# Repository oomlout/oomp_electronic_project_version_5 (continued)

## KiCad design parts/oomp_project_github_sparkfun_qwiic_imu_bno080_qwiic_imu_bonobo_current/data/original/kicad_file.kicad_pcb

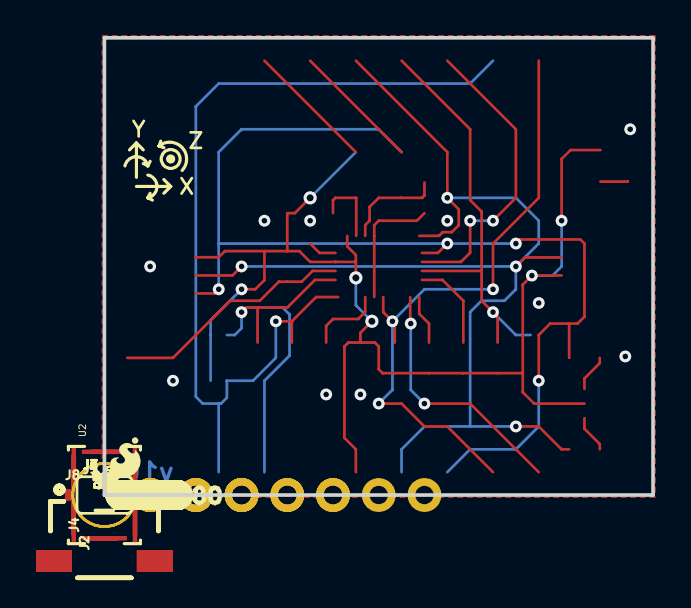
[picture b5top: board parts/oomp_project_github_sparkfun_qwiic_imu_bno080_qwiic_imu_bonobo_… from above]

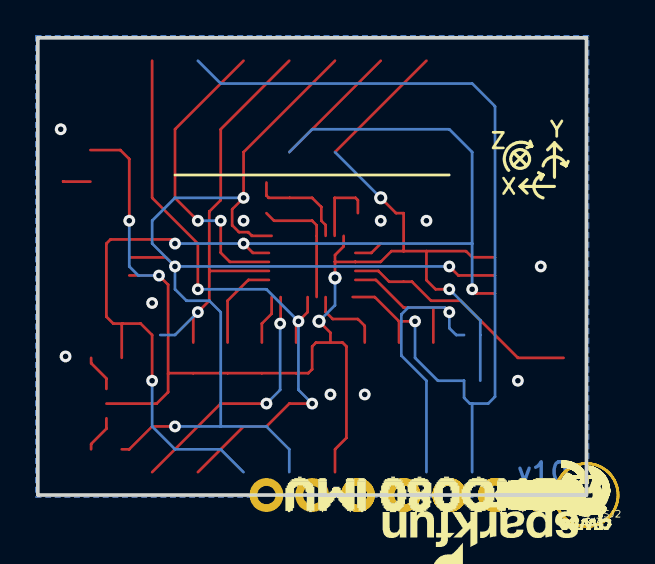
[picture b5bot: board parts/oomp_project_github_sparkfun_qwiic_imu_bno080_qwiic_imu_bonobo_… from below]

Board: 2 copper layers, 30.5 x 25.4 mm, 89 parts (35 on the bottom side), 19 nets.

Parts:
C1, C2, C4: 0.1uF; 0603
C3, C5: 22pF; 0603
D1: RED; LED-0603
FRAME1: FRAME-LETTER; CREATIVE_COMMONS
J1: 1X06_NO_SILK
J2, J4: SMD; 1X04_1MM_RA
J3: PTH; 1X04_NO_SILK
J5: 1X01_NO_SILK
J6: SPI; 1X08_NO_SILK
J7, J8: 1X02_NO_SILK
JP1, JP2, JP5, JP6: FIDUCIALUFIDUCIAL; MICRO-FIDUCIAL
JP3, JP4: STAND-OFF
LOGO1: OSHW-LOGOMINI; OSHW-LOGO-MINI
LOGO2: REVISION
LOGO4: SFE_LOGO_FLAME.1_INCH; SFE_LOGO_FLAME_.1
LOGO5: SFE_LOGO_NAME_FLAME.1_INCH; SFE_LOGO_NAME_FLAME_.1
R1, R3, R6, R7, R8: 10k; 0603
R2: 1k; 0603
R9, R10: 4.7k; 0603
R12, R13: 2.2k; 0603
SJ1: SMT-JUMPER_3_2-NC_PASTE_SILK
SJ2, SJ3, SJ4: SJ_2S-NO
U2: BNO080; LGA-28
U$1: (PWR)
U$2: BOOT2
U$3, U$4: #RST_
U$5, U$6: SCL
U$7, U$8: SDA
U$9, U$10: 3V3
U$11, U$50: 3V30
U$12, U$13: SCK0
U$14: PS03
U$15, U$16: GND
U$17, U$18: SI1
U$19, U$20: #WAK6
U$21: 3V32
U$22: RXI1
U$23: (I_SUPER2_C)
U$25, U$26: #INT0
U$27, U$28: PS14
U$29: PS05
U$30: ADR0
U$33: PS114
U$34: PS015
U$35: TXO0
U$39: UART8
U$40: GRN10
U$41: BLK9
U$42, U$43: GND1
U$44: BNO080_IMU11
U$46: BNO08012
U$47: IMU13
U$49, U$51: #RST7
U$52, U$53: #CS3
U$54, U$55: SO0
U$59: QWIIC#LABEL#FULL#M#PNG
Y1: 32.768kHz; CRYSTAL-SMD-3.2X1.5MM

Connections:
3.3V: C2.1, C4.1, D1.A, J1.3, J2.2, J3.2, J4.2, J6.2, R1.2, R3.2, R6.2, R9.2, R10.2, SJ1.2, SJ3.1, SJ4.1, U2.3, U2.28
ADDR/MOSI: J6.5, R3.1, SJ2.2, U2.17
CAP: C1.1, U2.9
GND: C1.2, C2.2, C3.2, C4.2, C5.2, J1.1, J2.1, J3.1, J4.1, J6.1, R2.1, R7.1, R8.1, SJ2.1, U2.2, U2.10, U2.25
unnamed: C5.1, U2.27, Y1.P$2
unnamed: C3.1, U2.26, Y1.P$1
unnamed: D1.C, R2.2
PS0/WAKE: J6.7, J8.2, R7.2, SJ3.2, U2.6
PS1: J8.1, R8.2, SJ4.2, U2.5
SCL/SCK/RX: J1.4, J2.4, J3.4, J4.4, J6.3, R12.1, U2.19
SCL_PU: R12.2, SJ1.1
SDA/MISO/TX: J1.5, J2.3, J3.3, J4.3, J6.4, R13.1, U2.20
SDA_PU: R13.2, SJ1.3
S_SCL: R10.1, U2.15
S_SDA: R9.1, U2.16
~BOOT: J5.1, R6.1, U2.4
~CS: J6.6, U2.18
~INT: J7.2, U2.14
~RST: J6.8, J7.1, R1.1, U2.11

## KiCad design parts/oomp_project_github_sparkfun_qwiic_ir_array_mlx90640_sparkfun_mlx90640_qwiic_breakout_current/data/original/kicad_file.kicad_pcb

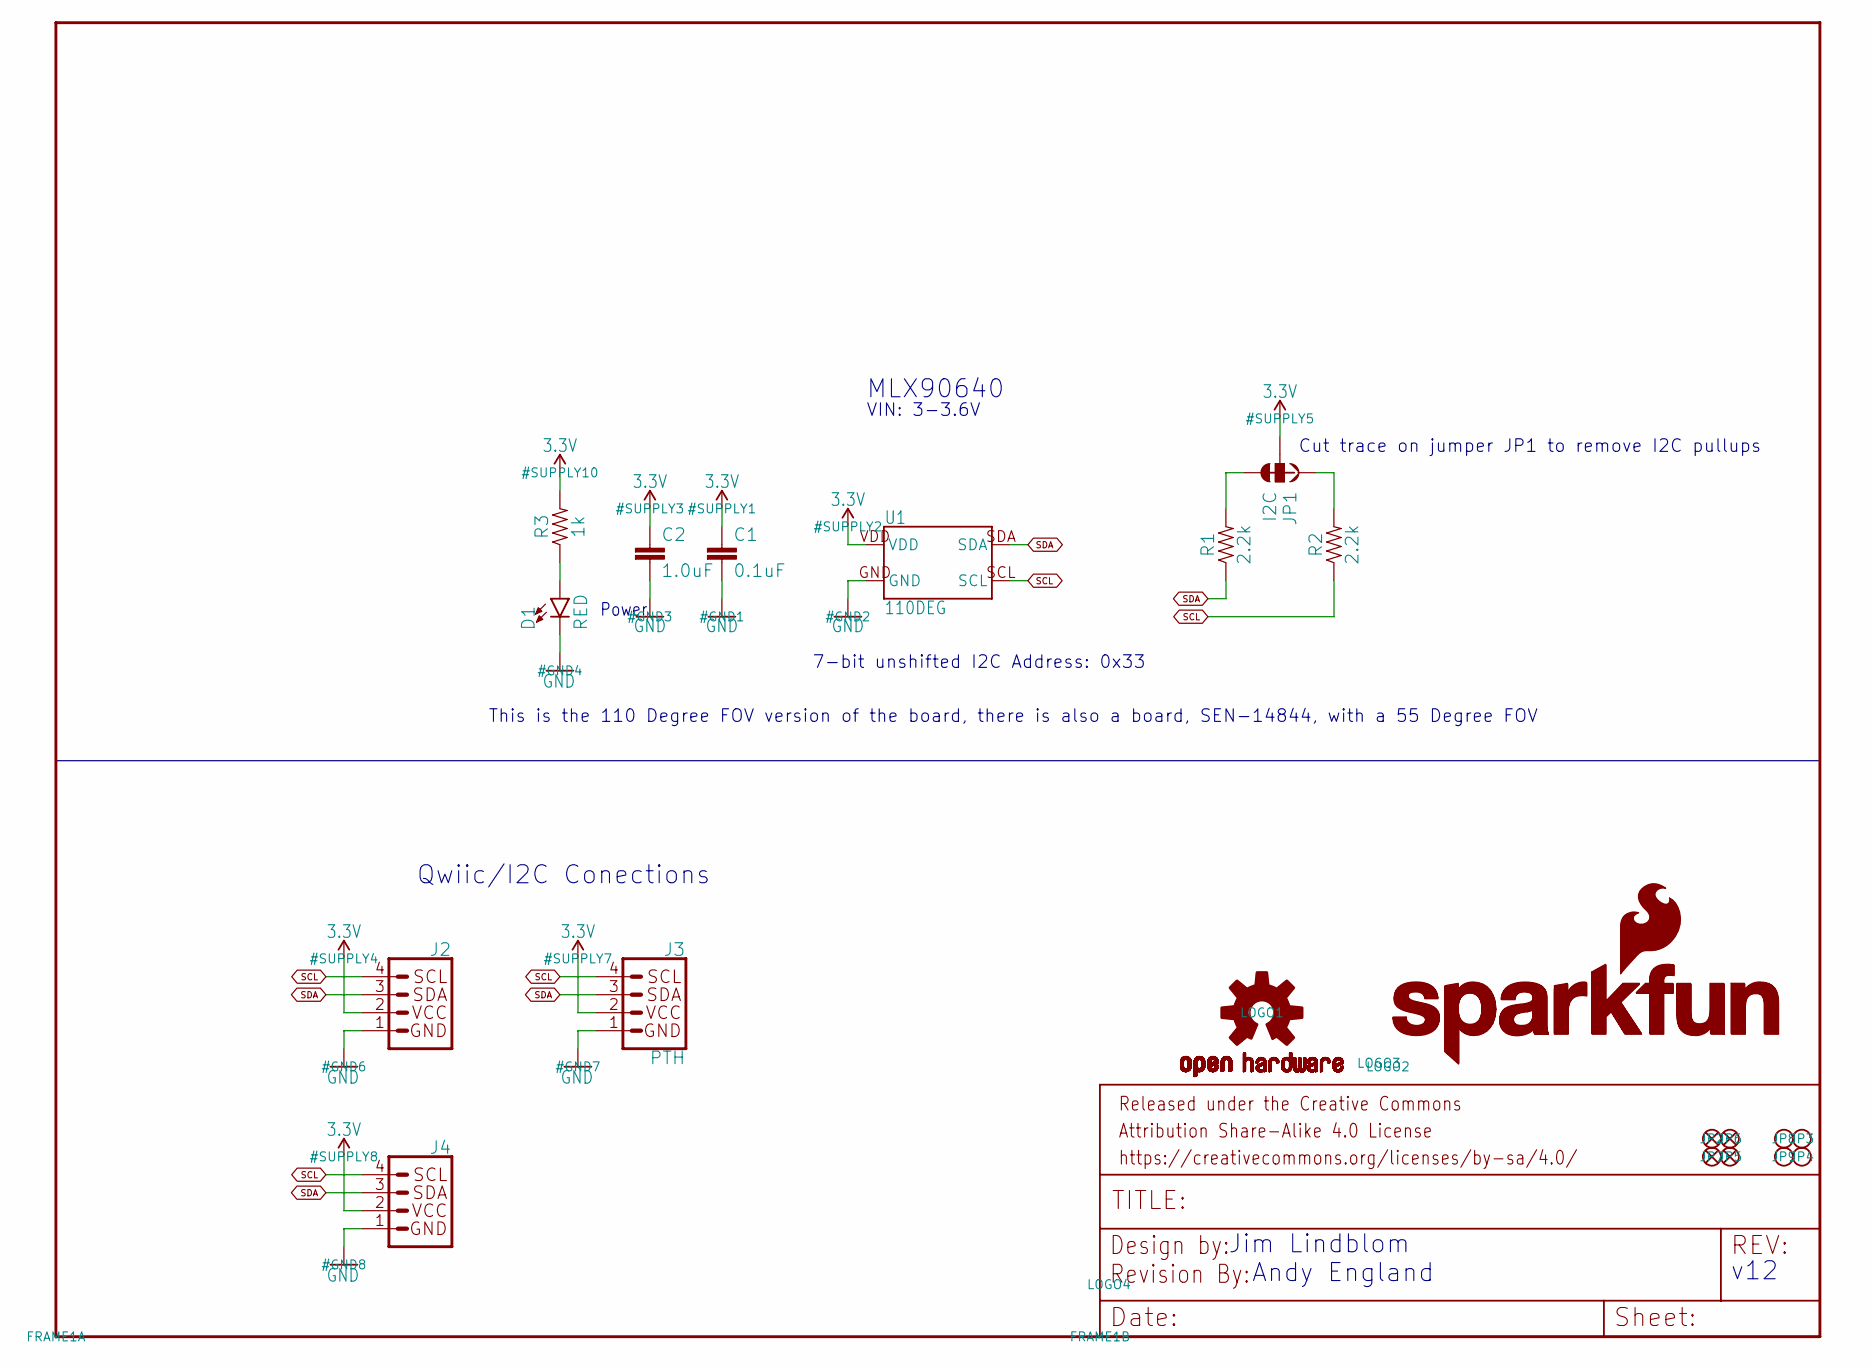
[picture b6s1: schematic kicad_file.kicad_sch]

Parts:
C1: 0.1uF; 0603
C2: 1.0uF; 0603
D1: RED; LED-0603
FRAME1: FRAME-LETTER; CREATIVE_COMMONS
J2, J4: QWIIC_CONNECTORJS-1MM; JST04_1MM_RA
J3: PTH; 1X04_NO_SILK
JP1: I2C; SMT-JUMPER_3_2-NC_TRACE_NO-SILK
JP2, JP5, JP6, JP7: FIDUCIALUFIDUCIAL; MICRO-FIDUCIAL
JP3, JP4, JP8, JP9: STAND-OFF
LOGO1: OSHW-LOGOMINI; OSHW-LOGO-MINI
LOGO2: SFE_LOGO_NAME_FLAME.1_INCH; SFE_LOGO_NAME_FLAME_.1
LOGO3: SFE_LOGO_NAME.1_INCH; SFE_LOGO_NAME_.1
LOGO4: REVISION
R1, R2: 2.2k; 0603
R3: 1k; 0603
U1: 110DEG; MLX90540_MLX90640

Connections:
3.3V: C1.1, C2.1, J2.2, J3.2 (VCC), J4.2, JP1.2, R3.2, U1.VDD
GND: C1.2, C2.2, D1.C, J2.1, J3.1 (GND), J4.1, U1.GND
unnamed: JP1.3, R1.2
unnamed: JP1.1, R2.2
unnamed: D1.A, R3.1
SCL: J2.4, J3.4 (SCL), J4.4, R2.1, U1.SCL
SDA: J2.3, J3.3 (SDA), J4.3, R1.1, U1.SDA

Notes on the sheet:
Cut trace on jumper JP1 to remove I2C pullups
7-bit unshifted I2C Address: 0x33
Jim Lindblom
VIN: 3-3.6V
MLX90640
Power
v12
This is the 110 Degree FOV version of the board, there is also a board, SEN-14844, with a 55 Degree FOV
Qwiic/I2C Conections
Andy England

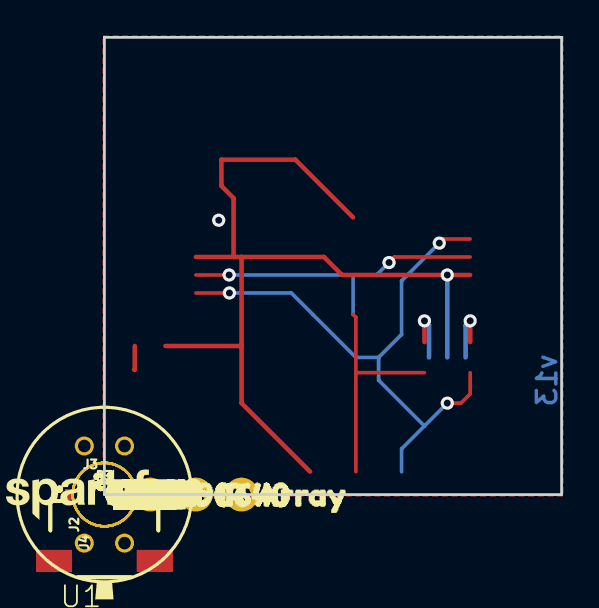
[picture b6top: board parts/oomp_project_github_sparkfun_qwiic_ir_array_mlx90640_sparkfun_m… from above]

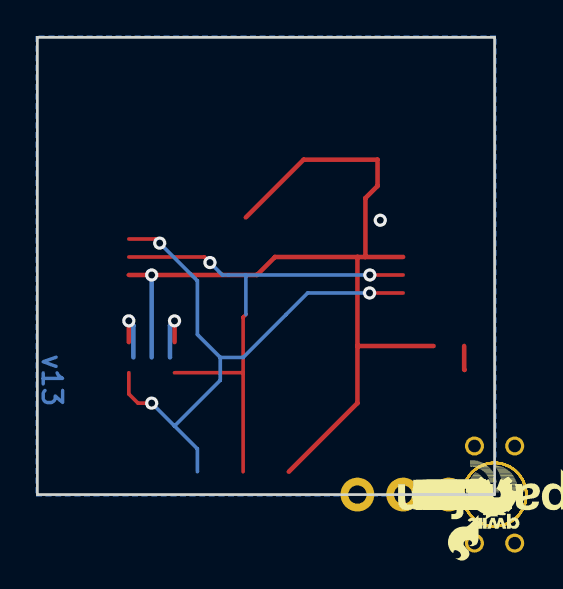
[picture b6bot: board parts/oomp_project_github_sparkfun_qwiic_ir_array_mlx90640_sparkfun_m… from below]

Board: 2 copper layers, 25.4 x 25.4 mm, 39 parts (11 on the bottom side), 7 nets.

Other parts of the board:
U$1, U$7: SDA-[)
U$3: 55X35#1
U$4, U$8: SCL-[)
U$5, U$9: 3.3V
U$6, U$10: GND-04
U$11: QWIIC-LOGO-SMALL
U$12: PWR-()-03
U$13: MLX906401
U$14: QWIIC_IR_ARRAY0
U$15: 110X75#0
U$16: I_SUPER2_C-()-03

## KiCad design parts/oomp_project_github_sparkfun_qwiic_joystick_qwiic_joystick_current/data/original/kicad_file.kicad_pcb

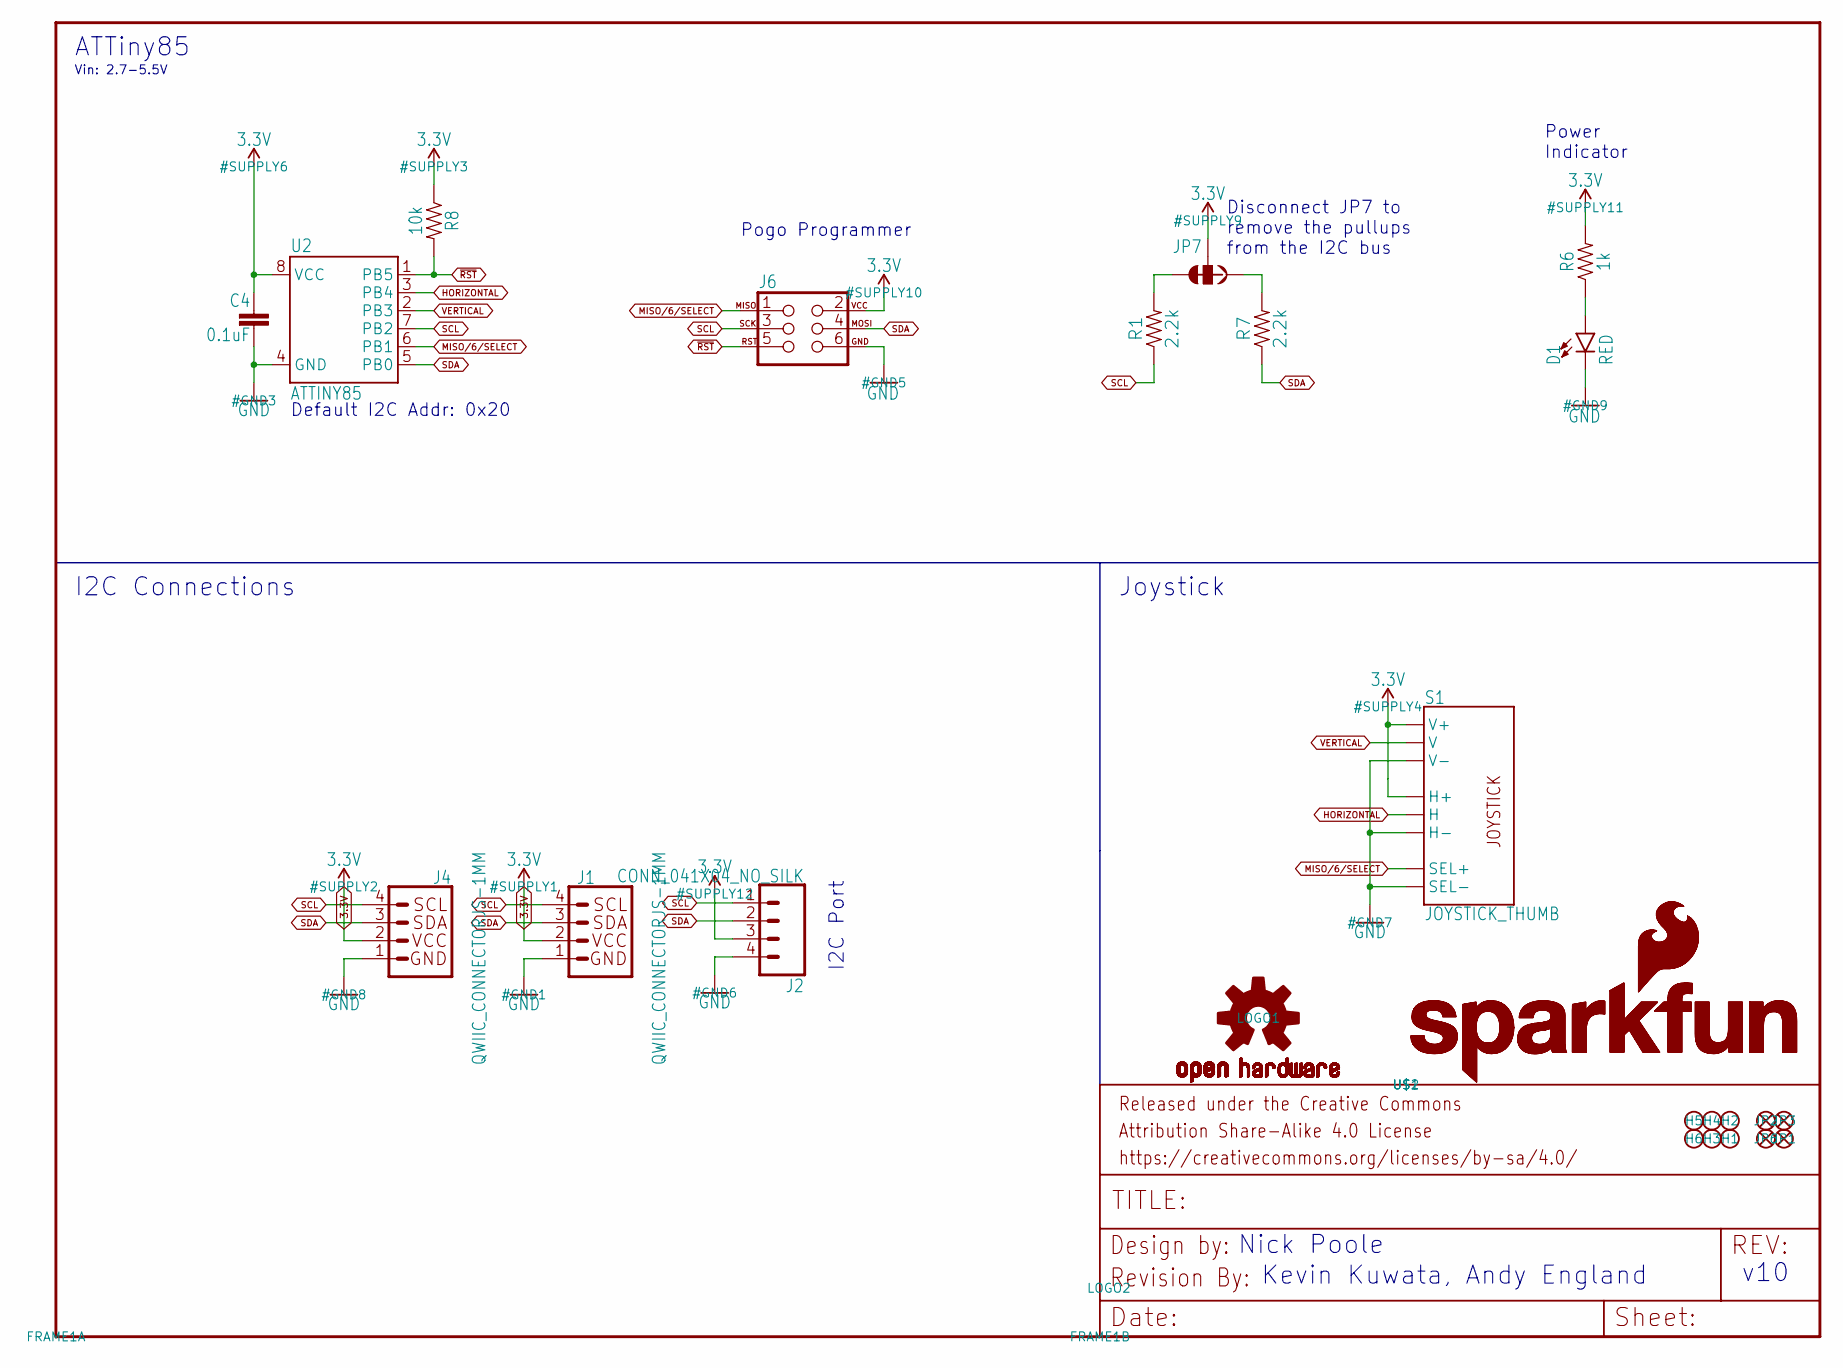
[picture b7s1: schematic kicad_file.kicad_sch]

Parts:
C4: 0.1uF; 0603
D1: RED; LED-0603
FRAME1: FRAME-LETTER; CREATIVE_COMMONS
H1, H2, H3, H4, H5, H6: STAND-OFF
J1, J4: QWIIC_CONNECTORJS-1MM; 1X04_1MM_RA
J2: CONN_041X04_NO_SILK; 1X04_NO_SILK
J6: AVR_SPI_PROG_3X2TESTPOINTS; 2X3_TEST_POINTS
JP1, JP2, JP3, JP6: FIDUCIALUFIDUCIAL; MICRO-FIDUCIAL
JP7: JUMPER-SMT_3_2-NC_TRACE_NO-SILK; SMT-JUMPER_3_2-NC_TRACE_NO-SILK
LOGO1: OSHW-LOGOMINI; OSHW-LOGO-MINI
LOGO2: REVISION
R1, R7: 2.2k; 0603
R6: 1k; 0603
R8: 10k; 0603
S1: JOYSTICK_THUMB; JOYSTICK
U2: ATTINY85
U$1, U$2: SFE_LOGO_NAME_FLAME.1_INCH; SFE_LOGO_NAME_FLAME_.1

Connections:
3.3V: C4.1, J1.2, J2.3, J4.2, J6.2, JP7.2, R6.2, R8.1, S1.H1 (H+), S1.V1 (V+), U2.8 (VCC)
GND: C4.2, D1.C, J1.1, J2.4, J4.1, J6.6, S1.B2A (SEL-), S1.H3 (H-), S1.V3 (V-), U2.4 (GND)
HORIZONTAL: S1.H2 (H), U2.3 (PB4)
MISO/6/SELECT: J6.1, S1.B1A (SEL+), U2.6 (PB1)
unnamed: D1.A, R6.1
unnamed: JP7.1, R7.2
unnamed: JP7.3, R1.2
SCL: J1.4, J2.1, J4.4, J6.3, R1.1, U2.7 (PB2)
SDA: J1.3, J2.2, J4.3, J6.4, R7.1, U2.5 (PB0)
VERTICAL: S1.V2 (V), U2.2 (PB3)
~RST: J6.5, R8.2, U2.1 (PB5)

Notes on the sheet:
I2C Connections
ATTiny85
Vin: 2.7-5.5V
Default I2C Addr: 0x20
I2C Port
Power Indicator
Disconnect JP7 to remove the pullups from the I2C bus
v10
Joystick
Pogo Programmer
Kevin Kuwata, Andy England
Nick Poole

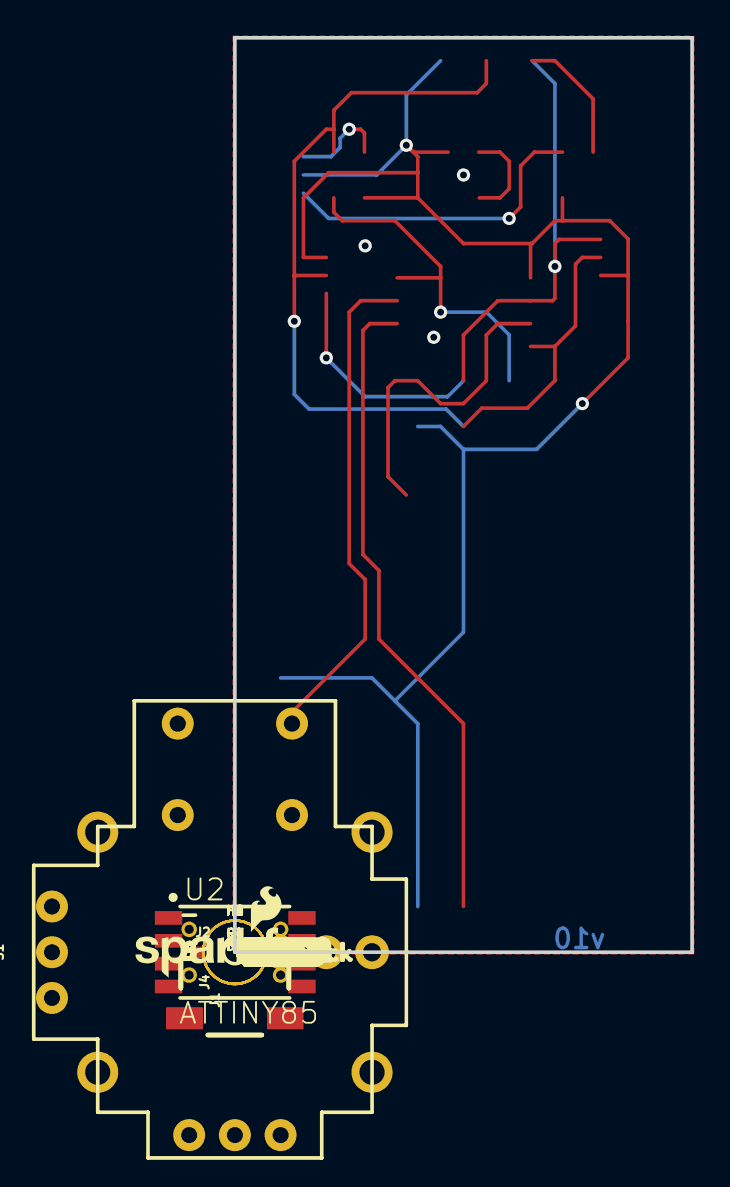
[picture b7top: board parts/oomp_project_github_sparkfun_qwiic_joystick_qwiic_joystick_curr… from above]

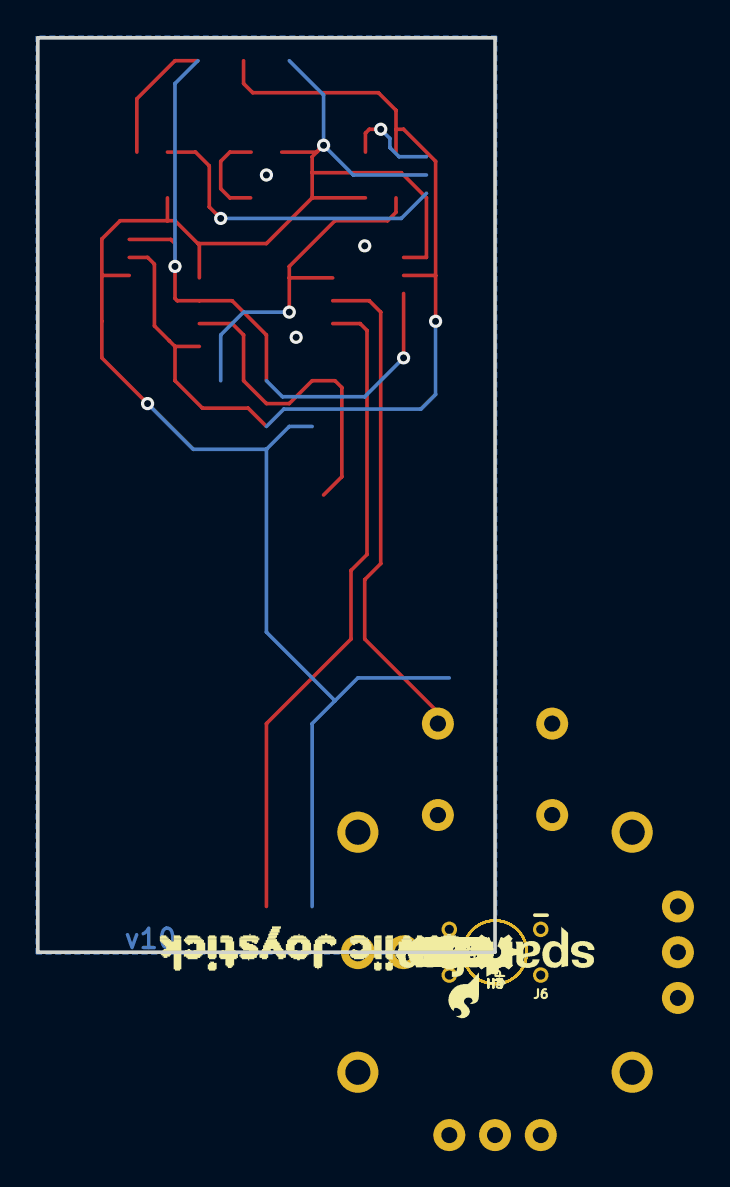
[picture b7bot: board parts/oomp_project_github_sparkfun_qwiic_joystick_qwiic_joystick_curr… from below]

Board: 2 copper layers, 25.4 x 50.8 mm, 43 parts (14 on the bottom side), 11 nets.

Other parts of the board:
U$3: QWIIC0
U$4: I2C_PU0
U$5: SDA0
U$6, U$8: GND4
U$7: ##V##1
U$9: SCL1
U$10: JOYSTICK0
U$11: SCL3
U$12: SDA2
U$13: QWIIC_JOYSTICK1
U$14: PWR-()-03
U$15: ##H##0
U$16, U$17: 3V35

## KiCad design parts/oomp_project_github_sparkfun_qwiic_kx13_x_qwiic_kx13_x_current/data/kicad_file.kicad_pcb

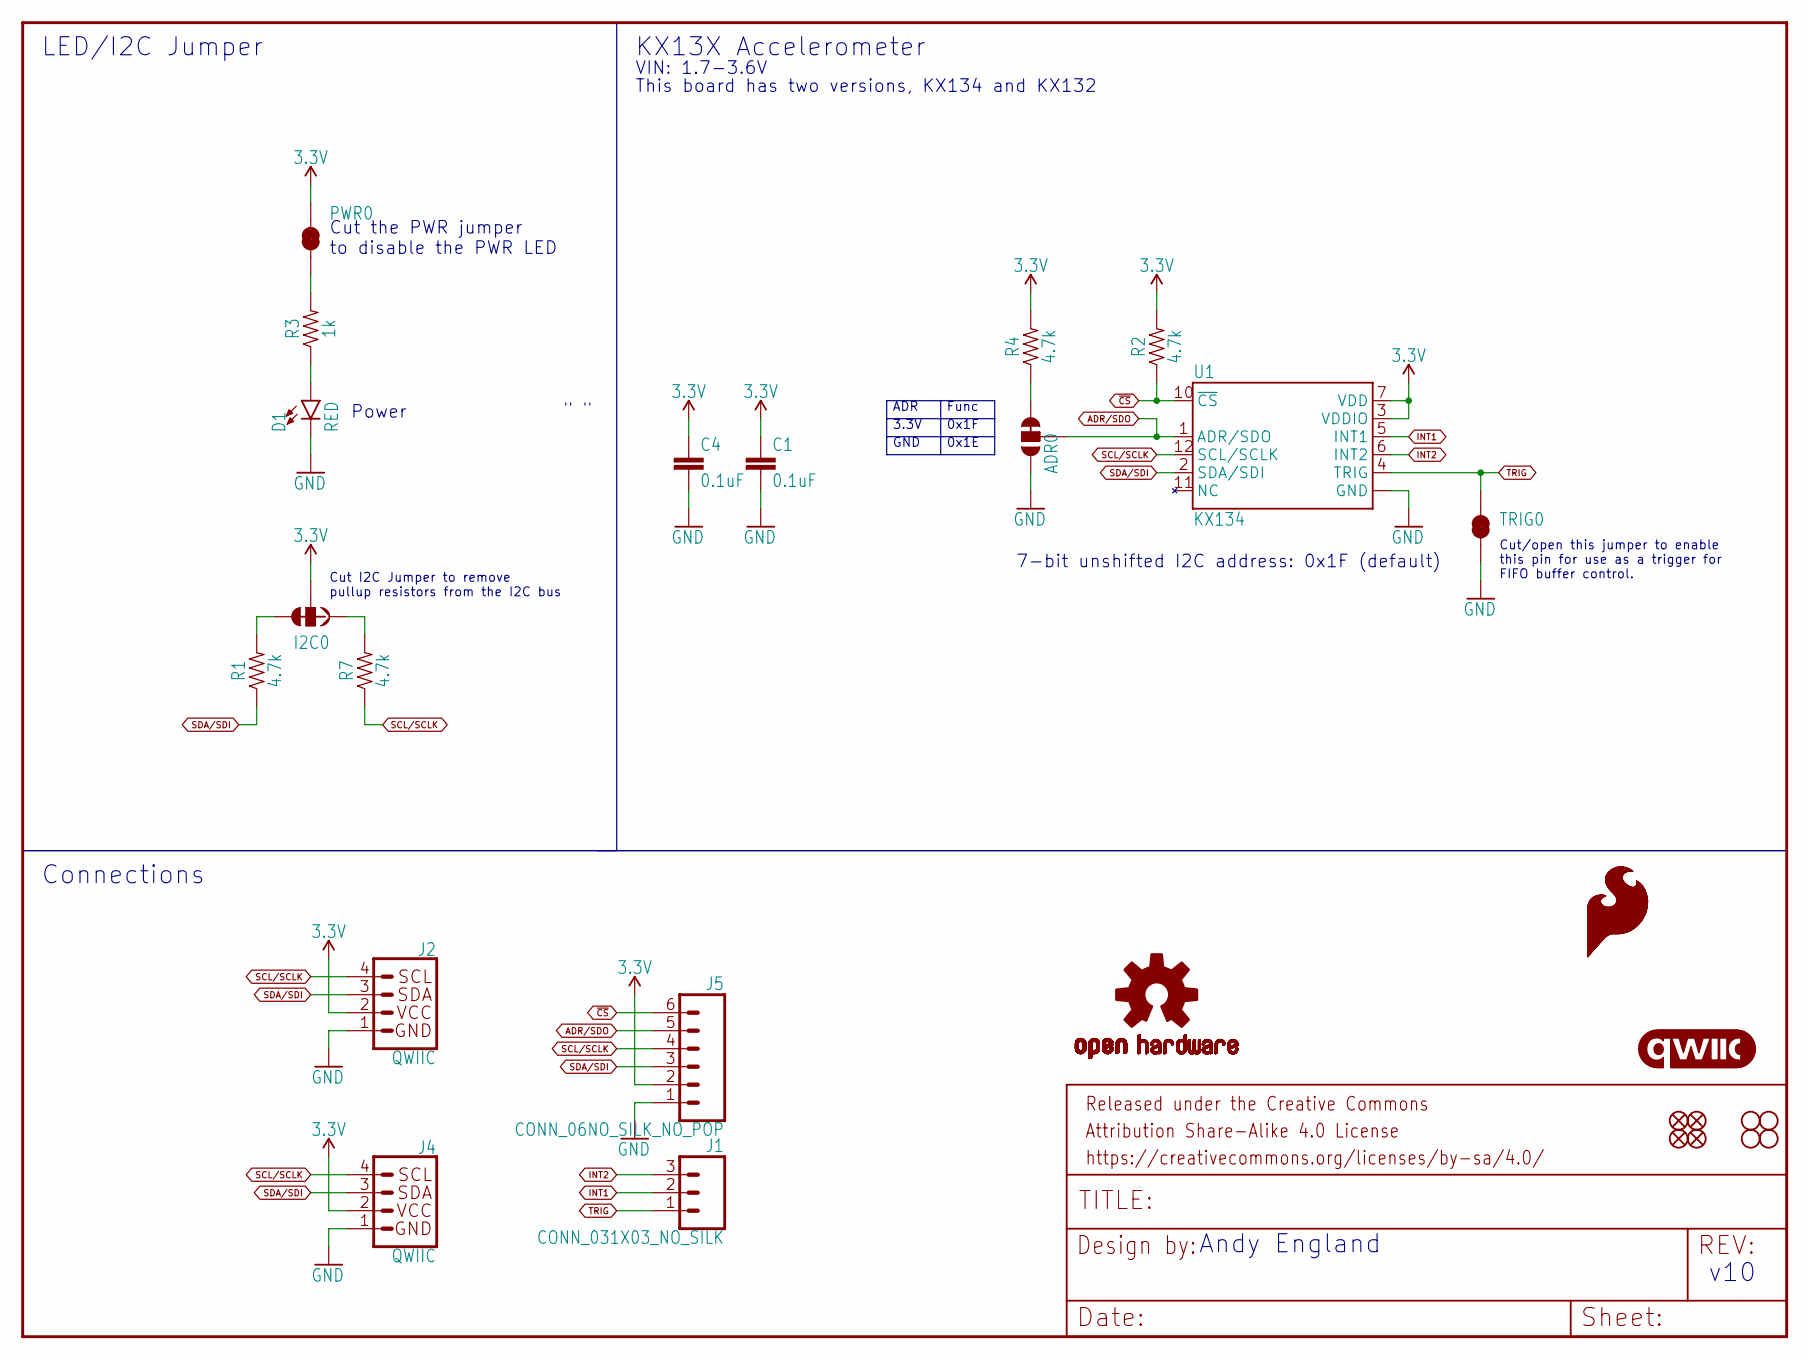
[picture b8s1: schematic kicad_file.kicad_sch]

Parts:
ADR0: JUMPER-SMT_3_1-NC_TRACE_SILK; SMT-JUMPER_3_1-NC_TRACE_SILK
C1, C4: 0.1uF; 0603
D1: RED; LED-0603
FRAME1: FRAME-LETTER; CREATIVE_COMMONS
I2C0: JUMPER-SMT_3_2-NC_TRACE_SILK; SMT-JUMPER_3_2-NC_TRACE_SILK
J1: CONN_031X03_NO_SILK; 1X03_NO_SILK
J2, J4: QWIIC; JST04_1MM_RA
J5: CONN_06NO_SILK_NO_POP; 1X06_NO_SILK
JP1, JP2, JP5, JP6: FIDUCIALUFIDUCIAL; MICRO-FIDUCIAL
JP3, JP4, JP7, JP8: STAND-OFF
LOGO1, LOGO2: SFE_LOGO_FLAME.1_INCH; SFE_LOGO_FLAME_.1
LOGO3: QWIIC_LOGO_4MM; QWIIC_4MM
LOGO5: OSHW-LOGOS; OSHW-LOGO-S
PWR0: JUMPER-SMT_2_NC_TRACE_SILK; SMT-JUMPER_2_NC_TRACE_SILK
R1, R2, R4, R7: 4.7k; 0603
R3: 1k; 0603
TRIG0: JUMPER-SMT_2_NC_TRACE_SILK; SMT-JUMPER_2_NC_TRACE_SILK
U1: KX134; KX13X

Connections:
3.3V: C1.1, C4.1, I2C0.2, J2.2, J4.2, J5.2, PWR0.2, R2.2, R4.2, U1.3 (VDDIO), U1.7 (VDD)
ADR/SDO: ADR0.2, J5.5, U1.1 (ADR/SDO)
GND: ADR0.1, C1.2, C4.2, D1.C, J2.1, J4.1, J5.1, TRIG0.2, U1.8 (GND), U1.9 (GND)
INT1: J1.2, U1.5 (INT1)
INT2: J1.3, U1.6 (INT2)
unnamed: PWR0.1, R3.2
unnamed: I2C0.3, R1.2
unnamed: D1.A, R3.1
unnamed: I2C0.1, R7.2
unnamed: ADR0.3, R4.1
SCL/SCLK: J2.4, J4.4, J5.4, R7.1, U1.12 (SCL/SCLK)
SDA/SDI: J2.3, J4.3, J5.3, R1.1, U1.2 (SDA/SDI)
TRIG: J1.1, TRIG0.1, U1.4 (TRIG)
~CS: J5.6, R2.1, U1.10 (~CS)

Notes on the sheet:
Func
Cut I2C Jumper to remove pullup resistors from the I2C bus
Andy England
VIN: 1.7-3.6V
Cut the PWR jumper to disable the PWR LED
Power
" "
GND
This board has two versions, KX134 and KX132
0x1E
3.3V
ADR
7-bit unshifted I2C address: 0x1F (default)
Connections
LED/I2C Jumper
KX13X Accelerometer
v10
Cut/open this jumper to enable this pin for use as a trigger for FIFO buffer control.
0x1F

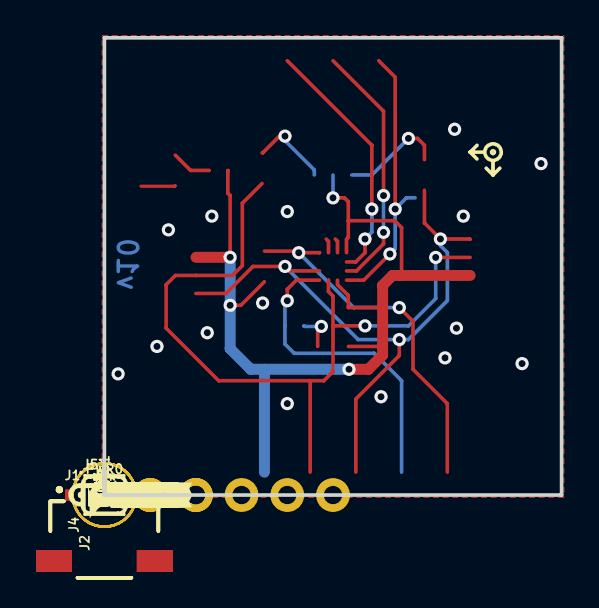
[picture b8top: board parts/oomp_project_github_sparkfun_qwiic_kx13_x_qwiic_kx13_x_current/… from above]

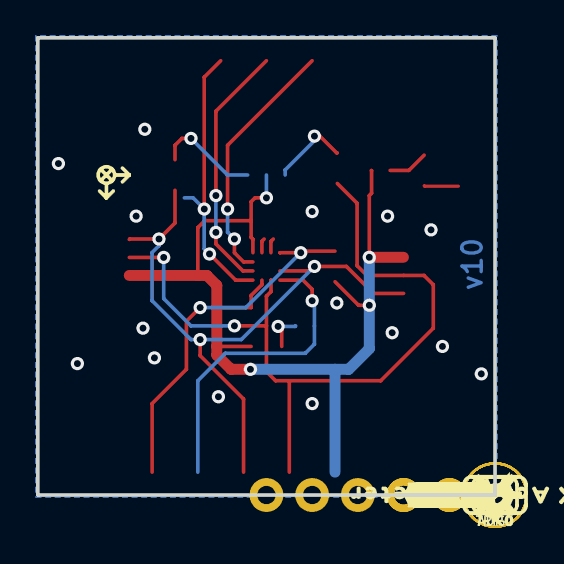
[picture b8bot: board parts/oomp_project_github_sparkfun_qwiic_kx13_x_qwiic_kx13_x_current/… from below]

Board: 2 copper layers, 25.4 x 25.4 mm, 63 parts (25 on the bottom side), 14 nets.

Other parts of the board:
U$1, U$28: X0
U$2: #SCL#0
U$3: #SDA#0
U$4, U$5: #3V3#0
U$6, U$7: #GND#0
U$8, U$9: ##CS##0
U$10: #ADR#0
U$11, U$15: #TRIG#0
U$12, U$13: #INT1#0
U$14: 0X1E0
U$17: #TRIG#2
U$18, U$19: #INT2#0
U$20: #ADR#3
U$21, U$29: Y0
U$22: #I2C#0
U$23: 0X1F0
U$24: #SDI#0
U$25: #SCLK#0
U$26: #SDO#0
U$27: KX13X_ACCELEROMETER14
U$30, U$32: Z0
U$31: PWR0
U$33: 1320
U$34: 1340
